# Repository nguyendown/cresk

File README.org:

* cresk
cresk is a caseless reversible ergonomic split keyboard.
** Features
- Cheap, reversible, and minimal size PCB
- Chip-shortage friendly, only one board is needed
- 34 keys, 3x5, 18 keys on the left, and 16 keys on the other
- Absolem stagger
- ZMK firmware
- OLED display, zmk widgets, interactive bongo cat
** Parts
- PCB set
- 1x STM32F401CC BlackPill board
- 1x I2C OLED display 128x32 (optional)
- 1x USB type C cable
- 1x RJ45 cable
- 2x RJ45 connectors
- 32x Diodes 1N4148 DO-35
- 34x MX switches
- 34x Keycaps 1U
- 6x Rubber bumpers
** Bootloader
A bootloader is required since entering DFU mode on a blackpill is
nearly impossible.

First, download [[https://github.com/adafruit/tinyuf2/releases][tinyuf2-stm32f401_blackpill-x.x.x]]. Extract it.

Enter DFU bootloader. Repeat these steps until your OS recognizes the
device.
- Hold BOOT0
- Press NRST
- Release BOOT0

I don't recommend entering the bootloader (or resetting) by replugging
(or powering off) the USB port as it may damage power regulator
component(s) on the blackpill. See Known issues.

You may increase the chance of success by heating it or using a USB to
TTL serial adaptor. See Known issues.

Then, upload tinyuf2 using ~dfu-util~
#+begin_src
dfu-util -d 0483:df11 -a 0 -s 0x08000000:leave -D tinyuf2-stm32f401_blackpill-x.x.x.bin
#+end_src
** Firmware
To flash a new firmware, double press NRST to enter UF2 bootloader.
Then copy .uf2 file to BlackPill drive.

Firmware is either built locally or using Github Actions.
*** Github Actions
- Fork the [[https://github.com/nguyendown/zmk-config][config]] repository
- Edit keymap ~config/boards/shields/cresk/cresk.keymap~
- Commit
- The new firmware will be on Actions tab.
*** Local build
- [[https://zmk.dev/docs/development/setup][Setup]] build environment
- Clone the [[https://github.com/nguyendown/zmk-config][config]] repository
- Edit keymap ~config/boards/shields/cresk/cresk.keymap~
- [[https://zmk.dev/docs/development/build-flash][Build]] firmware
#+begin_src
cd /path/to/zmk/app
west build -p -b blackpill_f401cc -- -DSHIELD=cresk -DZMK_CONFIG=/path/to/zmk-config/config
#+end_src
- The new firmware is at ~/path/to/zmk/app/build/zephyr/zmk.uf2~
*** Keymap
See\\
https://zmk.dev/docs/features/keymaps
** Assemble
Components placements.

#+ATTR_HTML: :title placement1
[[./res/placement1.jpg]]

#+ATTR_HTML: :title placement2
[[./res/placement2.jpg]]

Cut the bumpers in half then place them like this.

#+ATTR_HTML: :title bumpers1
[[./res/bumpers1.jpg]]

#+ATTR_HTML: :title bumpers2
[[./res/bumpers2.jpg]]

You may want to maximize repairability and extensibility by soldering
the blackpill like [[./res/blackpill-pins.jpg][this]].

[[./res/extend-sw17-sw18.jpg][Here]] is a more descriptive detailed instruction if you want to extend
SW17, and SW18 on the right side. Firmware for this mod:

https://github.com/nguyendown/zmk-config/tree/extend-sw17-sw18

I'll try duplex matrix in the next version.
** Known issues
*** Can't get into DFU mode
You may need to heat (or cool) it to be close to 25 degrees celsius.
See

https://forum.hobbycomponents.com/viewtopic.php?f=87&t=2947

A more reliable way is to use a USB to TTL serial adapter. Connect the
TX pin to A10 (USART1_RX) on the blackpill. Then enter DFU mode. It's
kinda ironic that you can just flash directly using USART.
*** Failed power component(s)
When I first received the board, I tried to get into DFU mode by
replugging the USB port instead of pressing NRST. My blackpill failed
after a few hundred tries. One or more components are probably
damaged. Maybe they were faulty in the first place. I have no idea.
Now it can't run on its own without an external 3.3v power source. I
may try an AMS1117 module later.

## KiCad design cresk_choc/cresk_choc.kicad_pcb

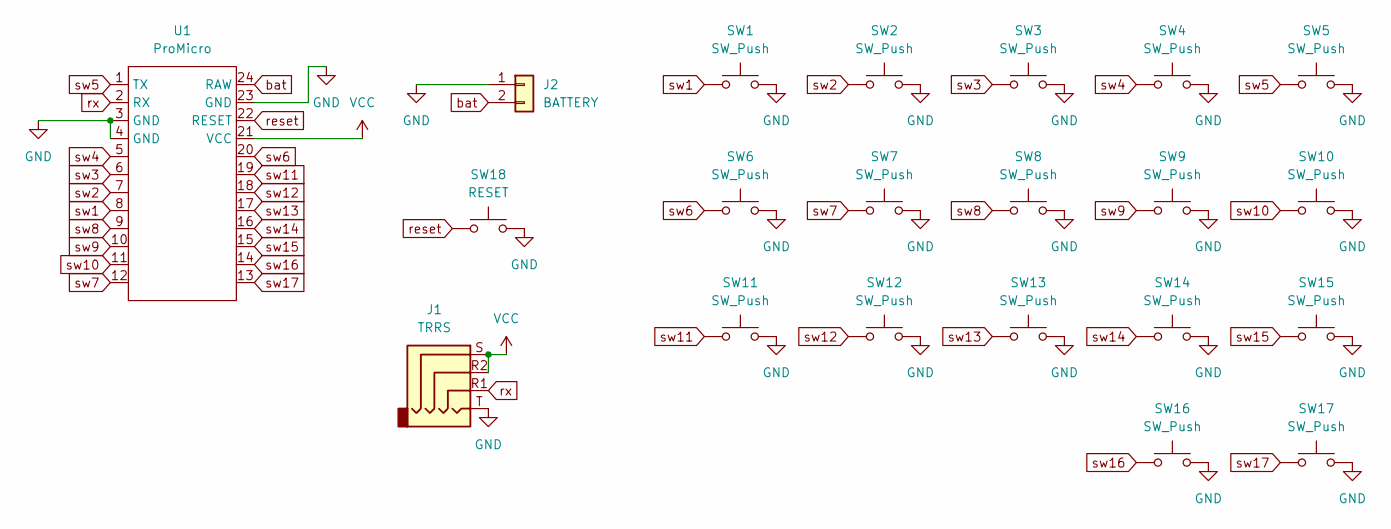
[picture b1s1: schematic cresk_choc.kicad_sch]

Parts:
J1: TRRS; PJ-320A_Reversible_Alt
J2: BATTERY; J_BATTERY
SW1, SW2, SW3, SW4, SW5, SW6, SW7, SW8, SW9, SW10, SW11, SW12, SW13, SW14, SW15, SW16, SW17: SW_Push; Kailh_Choc_Reversible
SW18: RESET; SW_PUSH_6mm
U1: ProMicro

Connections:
GND: J1.T, J2.1, SW1.2, SW2.2, SW3.2, SW4.2, SW5.2, SW6.2, SW7.2, SW8.2, SW9.2, SW10.2, SW11.2, SW12.2, SW13.2, SW14.2, SW15.2, SW16.2, SW17.2, SW18.2, U1.3 (GND), U1.4 (GND), U1.23 (GND)
VCC: J1.R2, J1.S, U1.21 (VCC)
bat: J2.2, U1.24 (RAW)
reset: SW18.1, U1.22 (RESET)
rx: J1.R1, U1.2 (RX)
sw1: SW1.1, U1.8
sw2: SW2.1, U1.7
sw3: SW3.1, U1.6
sw4: SW4.1, U1.5
sw5: SW5.1, U1.1 (TX)
sw6: SW6.1, U1.20
sw7: SW7.1, U1.12
sw8: SW8.1, U1.9
sw9: SW9.1, U1.10
sw10: SW10.1, U1.11
sw11: SW11.1, U1.19
sw12: SW12.1, U1.18
sw13: SW13.1, U1.17
sw14: SW14.1, U1.16
sw15: SW15.1, U1.15
sw16: SW16.1, U1.14
sw17: SW17.1, U1.13

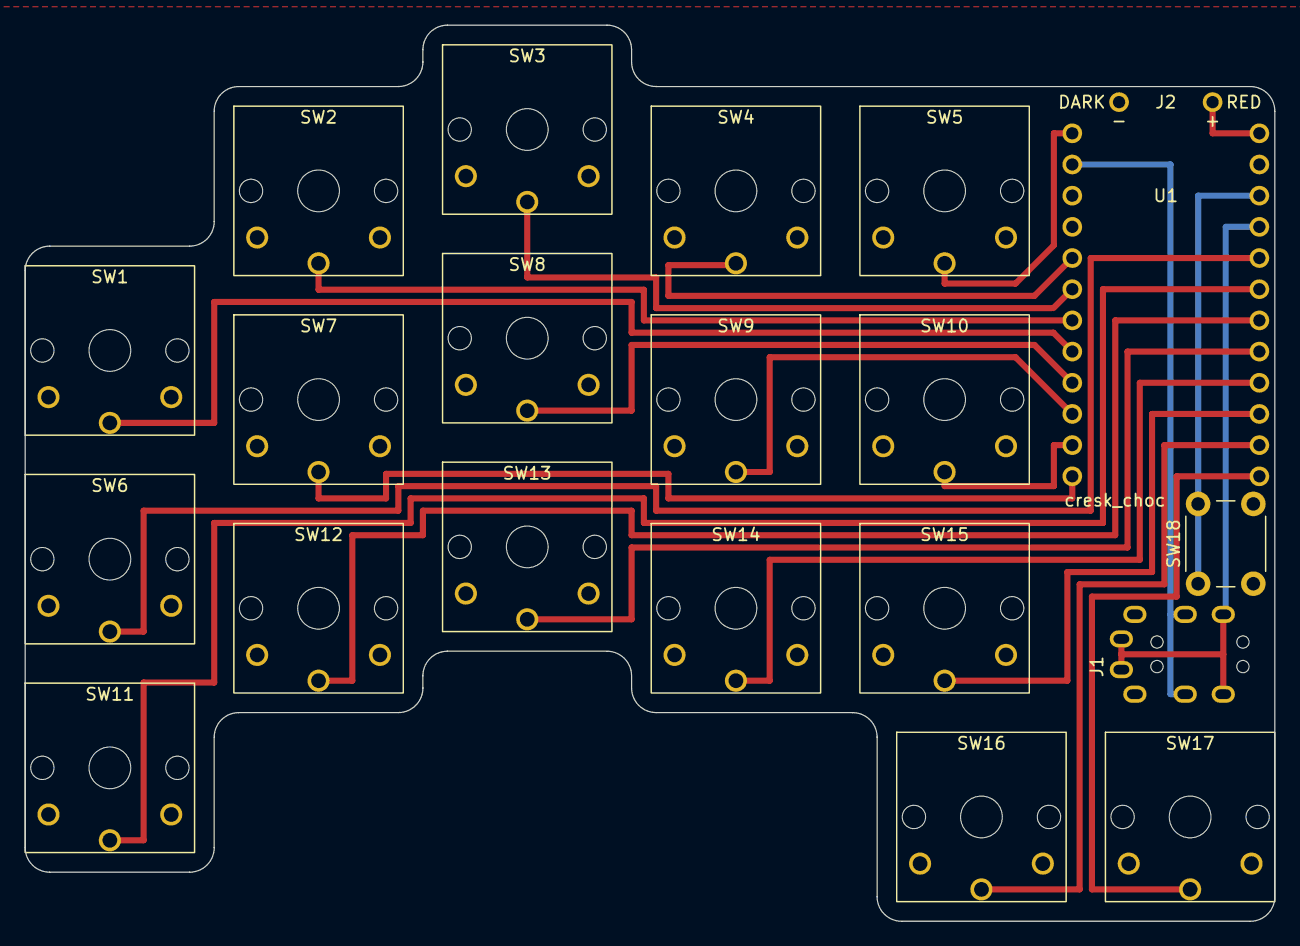
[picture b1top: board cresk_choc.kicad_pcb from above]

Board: 2 copper layers, 101.8 x 73.0 mm, 21 parts (0 on the bottom side), 22 nets.

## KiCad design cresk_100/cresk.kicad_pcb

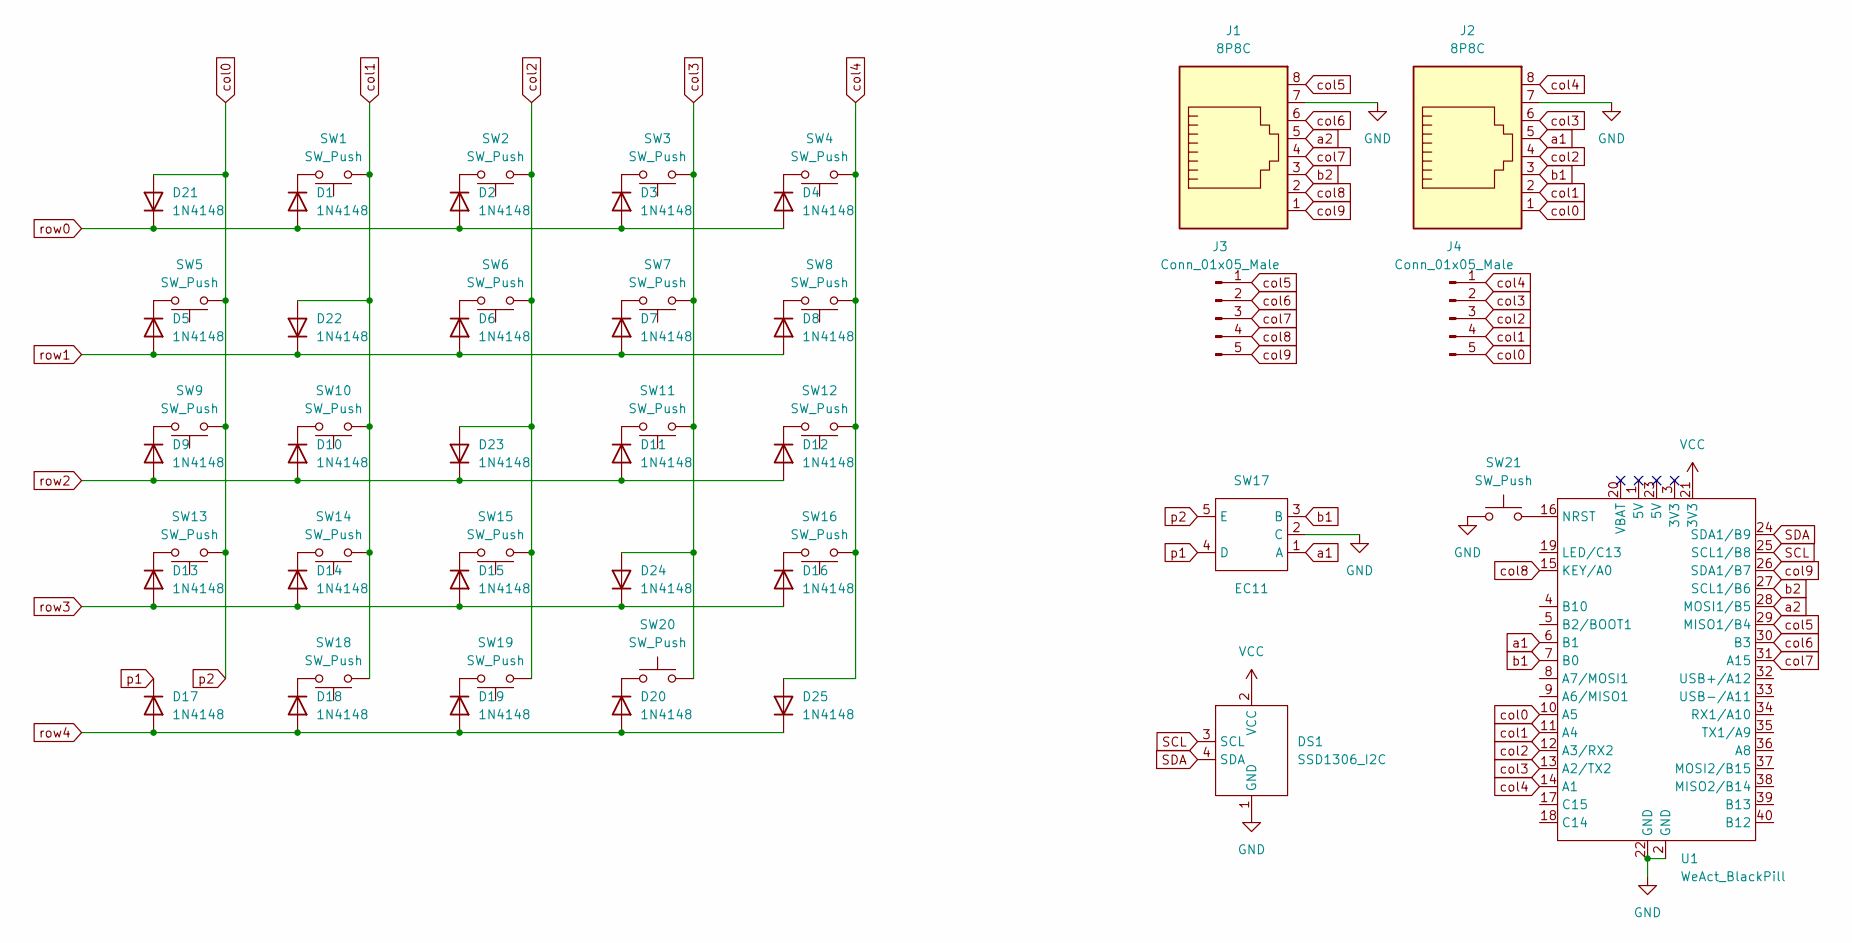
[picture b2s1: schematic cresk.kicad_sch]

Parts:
D1, D2, D3, D4, D5, D6, D7, D8, D9, D10, D11, D12, D13, D14, D15, D16, D17, D18, D19, D20, D21, D22, D23, D24, D25: 1N4148; D_DO-35
DS1: SSD1306_I2C
J1, J2: 8P8C; RJ45_Ninigi_GE
J3, J4: Conn_01x05_Male; J-01x05
SW1, SW2, SW3, SW4, SW5, SW6, SW7, SW8, SW9, SW10, SW11, SW12, SW13, SW14, SW15, SW16, SW18, SW19, SW20: SW_Push; SW_MX_1u_Reversible
SW17: EC11
SW21: SW_Push; SW_PUSH_6mm
U1: WeAct_BlackPill; WeAct_BlackPill_Flipped

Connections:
GND: DS1.1 (GND), J1.7, J2.7, SW17.2 (C), SW21.1, U1.2 (GND), U1.22 (GND)
unnamed: D1.1 (K), SW1.2
unnamed: D2.1 (K), SW2.2
unnamed: D3.1 (K), SW3.2
unnamed: D4.1 (K), SW4.2
unnamed: D5.1 (K), SW5.2
unnamed: D6.1 (K), SW6.2
unnamed: D7.1 (K), SW7.2
unnamed: D8.1 (K), SW8.2
unnamed: D9.1 (K), SW9.2
unnamed: D10.1 (K), SW10.2
unnamed: D11.1 (K), SW11.2
unnamed: D12.1 (K), SW12.2
unnamed: D13.1 (K), SW13.2
unnamed: D14.1 (K), SW14.2
unnamed: D15.1 (K), SW15.2
unnamed: D16.1 (K), SW16.2
unnamed: D18.1 (K), SW18.2
unnamed: D19.1 (K), SW19.2
unnamed: D20.1 (K), SW20.1
unnamed: SW21.2, U1.16 (NRST)
SCL: DS1.3 (SCL), U1.25 (SCL1/B8)
SDA: DS1.4 (SDA), U1.24 (SDA1/B9)
VCC: DS1.2 (VCC), U1.21 (3V3)
a1: J2.5, SW17.1 (A), U1.6 (B1)
a2: J1.5, U1.28 (MOSI1/B5)
b1: J2.3, SW17.3 (B), U1.7 (B0)
b2: J1.3, U1.27 (SCL1/B6)
col0: D21.2 (A), J2.1, J4.5, SW5.1, SW9.1, SW13.1, SW17.5 (E), U1.10 (A5)
col1: D22.2 (A), J2.2, J4.4, SW1.1, SW10.1, SW14.1, SW18.1, U1.11 (A4)
col2: D23.2 (A), J2.4, J4.3, SW2.1, SW6.1, SW15.1, SW19.1, U1.12 (A3/RX2)
col3: D24.2 (A), J2.6, J4.2, SW3.1, SW7.1, SW11.1, SW20.2, U1.13 (A2/TX2)
col4: D25.2 (A), J2.8, J4.1, SW4.1, SW8.1, SW12.1, SW16.1, U1.14 (A1)
col5: J1.8, J3.1, U1.29 (MISO1/B4)
col6: J1.6, J3.2, U1.30 (B3)
col7: J1.4, J3.3, U1.31 (A15)
col8: J1.2, J3.4, U1.15 (KEY/A0)
col9: J1.1, J3.5, U1.26 (SDA1/B7)
p1: D17.1 (K), SW17.4 (D)
row0: D1.2 (A), D2.2 (A), D3.2 (A), D4.2 (A), D21.1 (K)
row1: D5.2 (A), D6.2 (A), D7.2 (A), D8.2 (A), D22.1 (K)
row2: D9.2 (A), D10.2 (A), D11.2 (A), D12.2 (A), D23.1 (K)
row3: D13.2 (A), D14.2 (A), D15.2 (A), D16.2 (A), D24.1 (K)
row4: D17.2 (A), D18.2 (A), D19.2 (A), D20.2 (A), D25.1 (K)

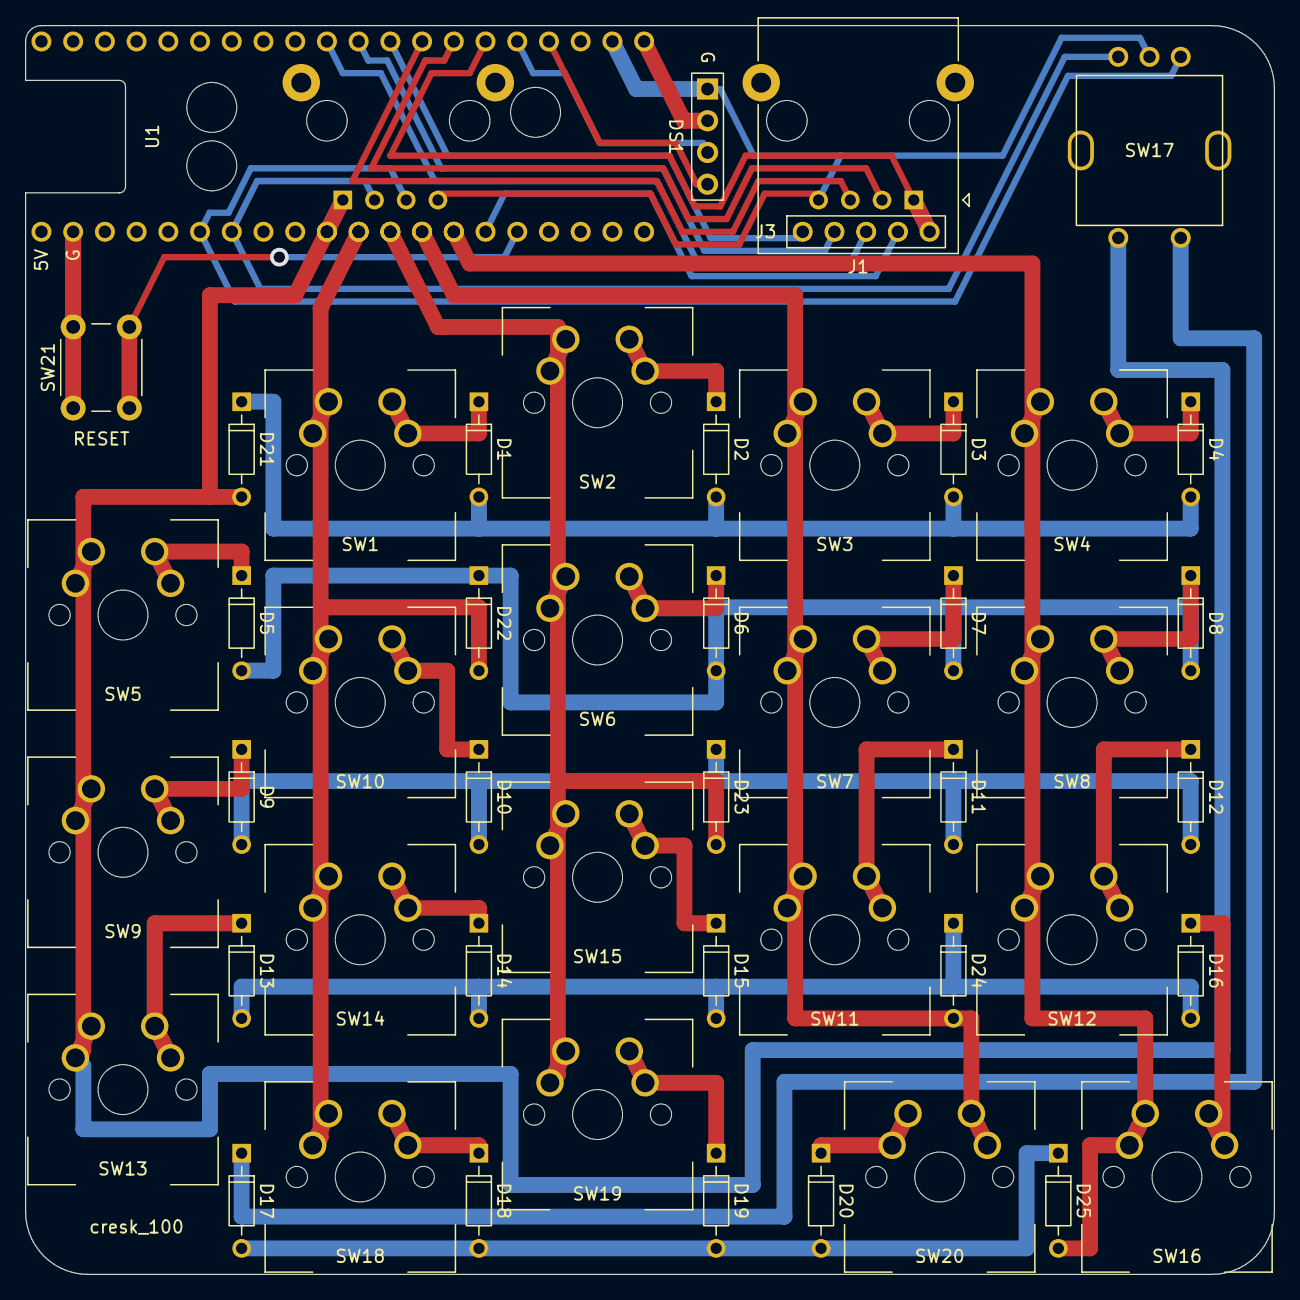
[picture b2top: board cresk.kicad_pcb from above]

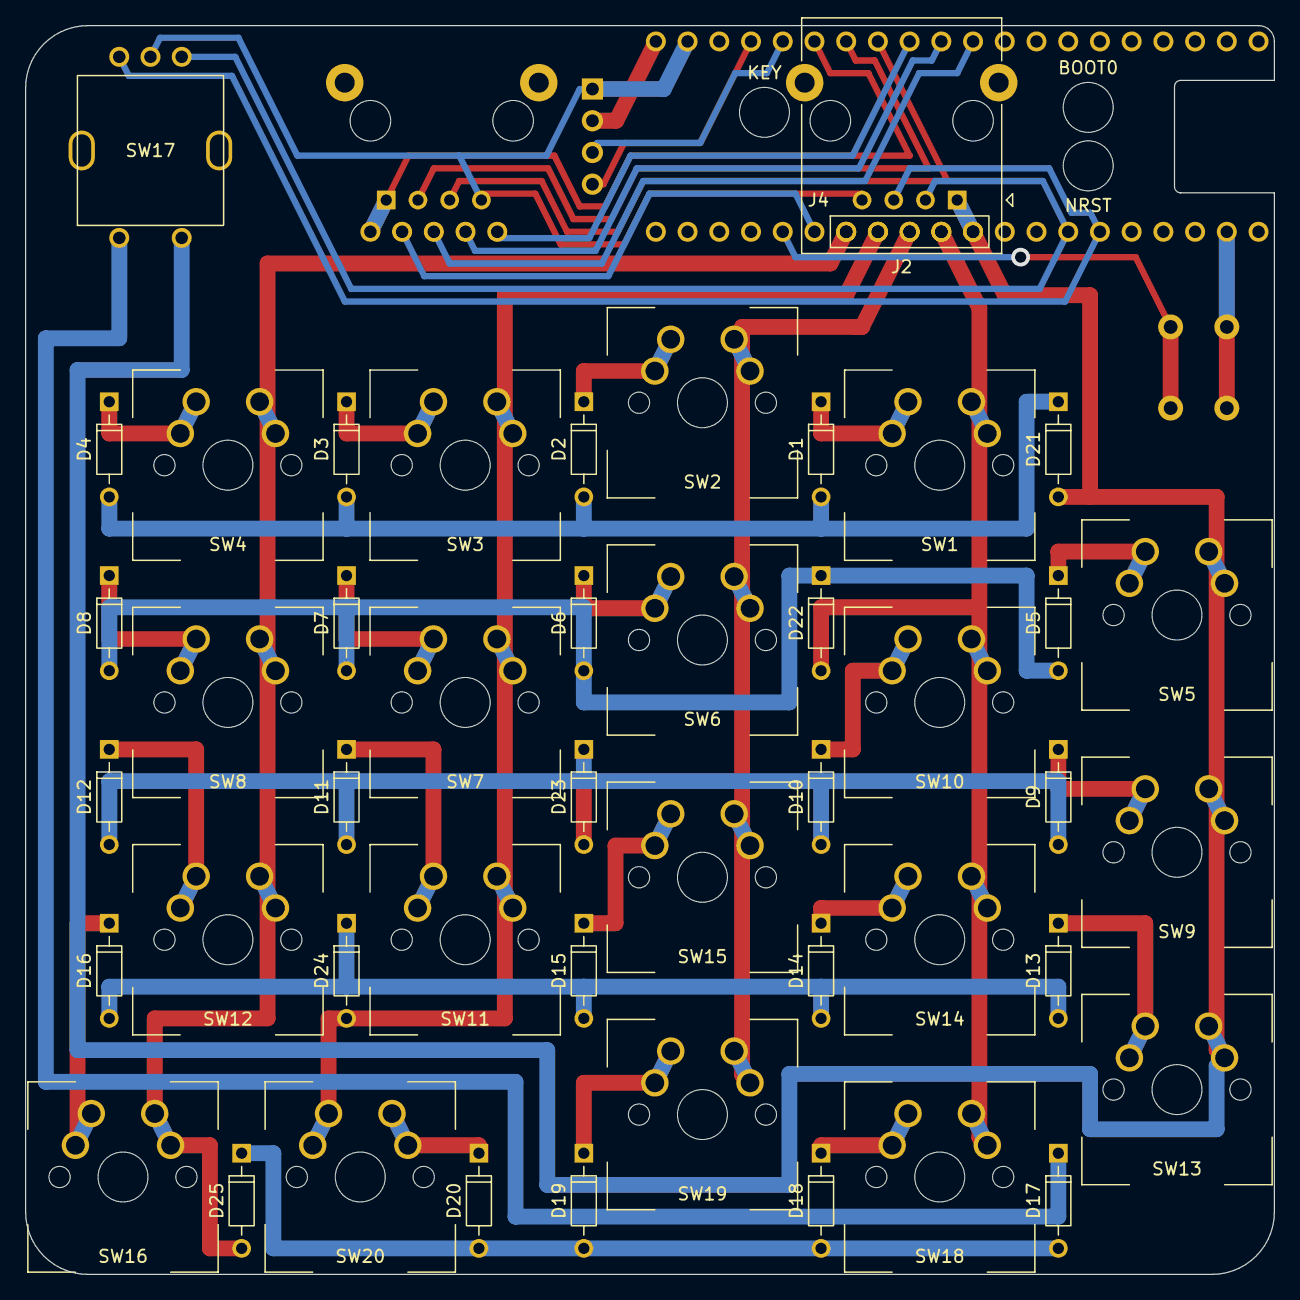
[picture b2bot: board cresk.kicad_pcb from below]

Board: 2 copper layers, 100.0 x 100.0 mm, 52 parts (2 on the bottom side), 44 nets.

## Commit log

2022-05-08 init: a keyboard of the future
2022-05-08 fix(footprint): add silkscreen at ssd1306 pin header
2022-05-08 feat(pcb): reposition row3 diodes
2022-05-10 feat: add description
2022-05-10 feat: add name
2022-06-09 test: org test
2022-06-09 test: org image test
2022-06-09 test: add 2 image
2022-06-09 test: test images
2022-06-09 test: why not you stupid bastard
2022-06-09 test: why isn't it possible
2022-06-09 test: it's possible
2022-06-09 test: bumpers placements
2022-06-14 test: fix things
2022-06-14 test: fix
2022-06-15 fix: inline code
2022-06-16 test: fixes
2022-06-16 test: fixtdrestderna
2022-06-16 test: more fixes
2022-06-16 test: descriptive detailed
2022-07-19 fix(footprint): increase pin hole, fix mx switch pin
2022-07-19 feat: replace cresk with cresk v2
2022-08-11 symbol: remove redundant symbols
2022-08-12 cresk(pcb): full pad blackpill
2022-08-18 cresk_100: cresk v2 will now be cresk_100
2022-08-18 cresk_100: libs stay
2022-08-18 cresk_choc: demo
2022-08-18 cresk_choc: test drill sizes
2022-08-18 cresk_choc: gerber options
2022-08-18 gitignore add gerber output folder
2022-08-19 cresk_choc: finish routing
2022-08-19 footprint: add b silkscreen
2022-08-19 cresk_choc: update kailh choc footprint
2022-08-20 cresk_choc: update sw16 sw17 tracks
2022-08-23 footprint: revert position of NRST and BOOT0
2022-08-23 cresk_100: update through hole size
    Pad size to 1.6 mm and drill to 1 mm.
2022-08-24 cresk_100: change pin mapping
    Make it compatible with non flipped BlackPill, and possibly ProMicro.
2022-08-24 cresk_100: revert mx spacing to 19 mm
    Was 18.75 mm. Works.
2022-08-24 cresk_100: BlackPill footprint text rotation, USB edge cuts
2022-08-25 cresk_100: describe board dimension, staggers and more
2022-08-25 cresk_100: correct OLED footprint
2022-08-25 cresk_100: fix texts on edge cuts layer
2022-09-18 cresk_choc: update kailh choc footprint
    Silkscreen rectangle from 14.5 to 13.8.
2022-09-19 cresk_choc: move thumbs 0.5 mm to the right
    Index to thumb distance is increased from 19.5 mm to 20 mm.
2022-10-16 cresk_choc: remove copper fill
    Copper fills are not git friendly. Must be refilled before generating
    fab outputs.
2022-10-16 cresk_choc: edit name
